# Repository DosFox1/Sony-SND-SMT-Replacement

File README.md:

# Sony-SND-SMT-Replacement
BETA -
A replacement for the Sony SND IC (part number 343-0045-A) as used on the Macintosh Plus, SE and others, using SMD parts.

# So what is it?
This is a variant of my existing Sony SND replacement, however, it uses purely SMD parts. 
My original repo for the through hole variant can be found here:
https://github.com/DosFox1/Sony-SND-THT-Replacement

The design is effectively the same - tincluding the annoying requirement to tap -12v from the board. If it aint broke, don't fix it!
Turns out removing -12v makes the audio output unhappy. So make sure you leave that in. 
POR works though - just make sure the pullup resistor from the POR switch is removed (I.E, R21 on the Mac Plus board). 

**NOTE - This is Completely Untested**
# Bill Of Materials:
```blocks
Part     Value          Device                       Package  Library                Sheet

C1       100n 16V       100N_CAP_0603                C0603    Capacitors SMD         1
C2       100n 16V       100N_CAP_0603                C0603    Capacitors SMD         1
C3       100n 16V       100N_CAP_0603                C0603    Capacitors SMD         1
C4       100n 16V       100N_CAP_0603                C0603    Capacitors SMD         1
C5       1u 16V         1U_CAP_0603                  C0603    Capacitors SMD         1
C6       100n 16V       100N_CAP_0603                C0603    Capacitors SMD         1
C7       470p           470P_CAP_0603                C0603    Capacitors SMD         1
C8       1n 50V         1N_CAP_0603                  C0603    Capacitors SMD         1
C9       100n 16V       100N_CAP_0603                C0603    Capacitors SMD         1
C10      100n 16V       100N_CAP_0603                C0603    Capacitors SMD         1
C11      220p           220P_CAP_0603                C0603    Capacitors SMD         1
C12      100n 16V       100N_CAP_0603                C0603    Capacitors SMD         1
D1       5.1V           DIODE-ZENER-MMSZ5231B        SOD-123  SparkFun-DiscreteSemi  1
IC1      TL072          OPAMP-DUALU                  SO08     SparkFun-IC-Amplifiers 1
IC2      4016D          4016D                        SO14     40xx                   1
IC3      NE555DRG4      555_SOIC8                    SOIC8    ICs                    1
IC4      74LVC1G06DBV   74LVC1G06DBV                 SOT23-5  74xx-little-us         1
IC5      Turned pins    SND THT turned pins          DIP16    Pins                   1
Q1       MMBT3906       TRANS_PNP-PMBT3906|MMBT3906L SOT23-3  SparkFun-DiscreteSemi  1
Q2       MMBT3904       TRANS_NPN-MMBT2222AL         SOT23-3  SparkFun-DiscreteSemi  1
R1       1M             GENERIC_RESISTOR_0603        R0603    Resistors SMD          1
R2       1M             GENERIC_RESISTOR_0603        R0603    Resistors SMD          1
R3       6K8            GENERIC_RESISTOR_0603        R0603    Resistors SMD          1
R4       47K            47K_RESISTOR                 R0603    Resistors SMD          1
R5       1k             1K_RESISTOR_0603             R0603    Resistors SMD          1
R6       47K            47K_RESISTOR                 R0603    Resistors SMD          1
R7       68K            GENERIC_RESISTOR_0603        R0603    Resistors SMD          1
R8       150K           GENERIC_RESISTOR_0603        R0603    Resistors SMD          1
R9       470K           GENERIC_RESISTOR_0603        R0603    Resistors SMD          1
R10      470K           GENERIC_RESISTOR_0603        R0603    Resistors SMD          1
R11      200K           GENERIC_RESISTOR_0603        R0603    Resistors SMD          1
R12      150R           150R_RESISTOR_0603           R0603    Resistors SMD          1
```

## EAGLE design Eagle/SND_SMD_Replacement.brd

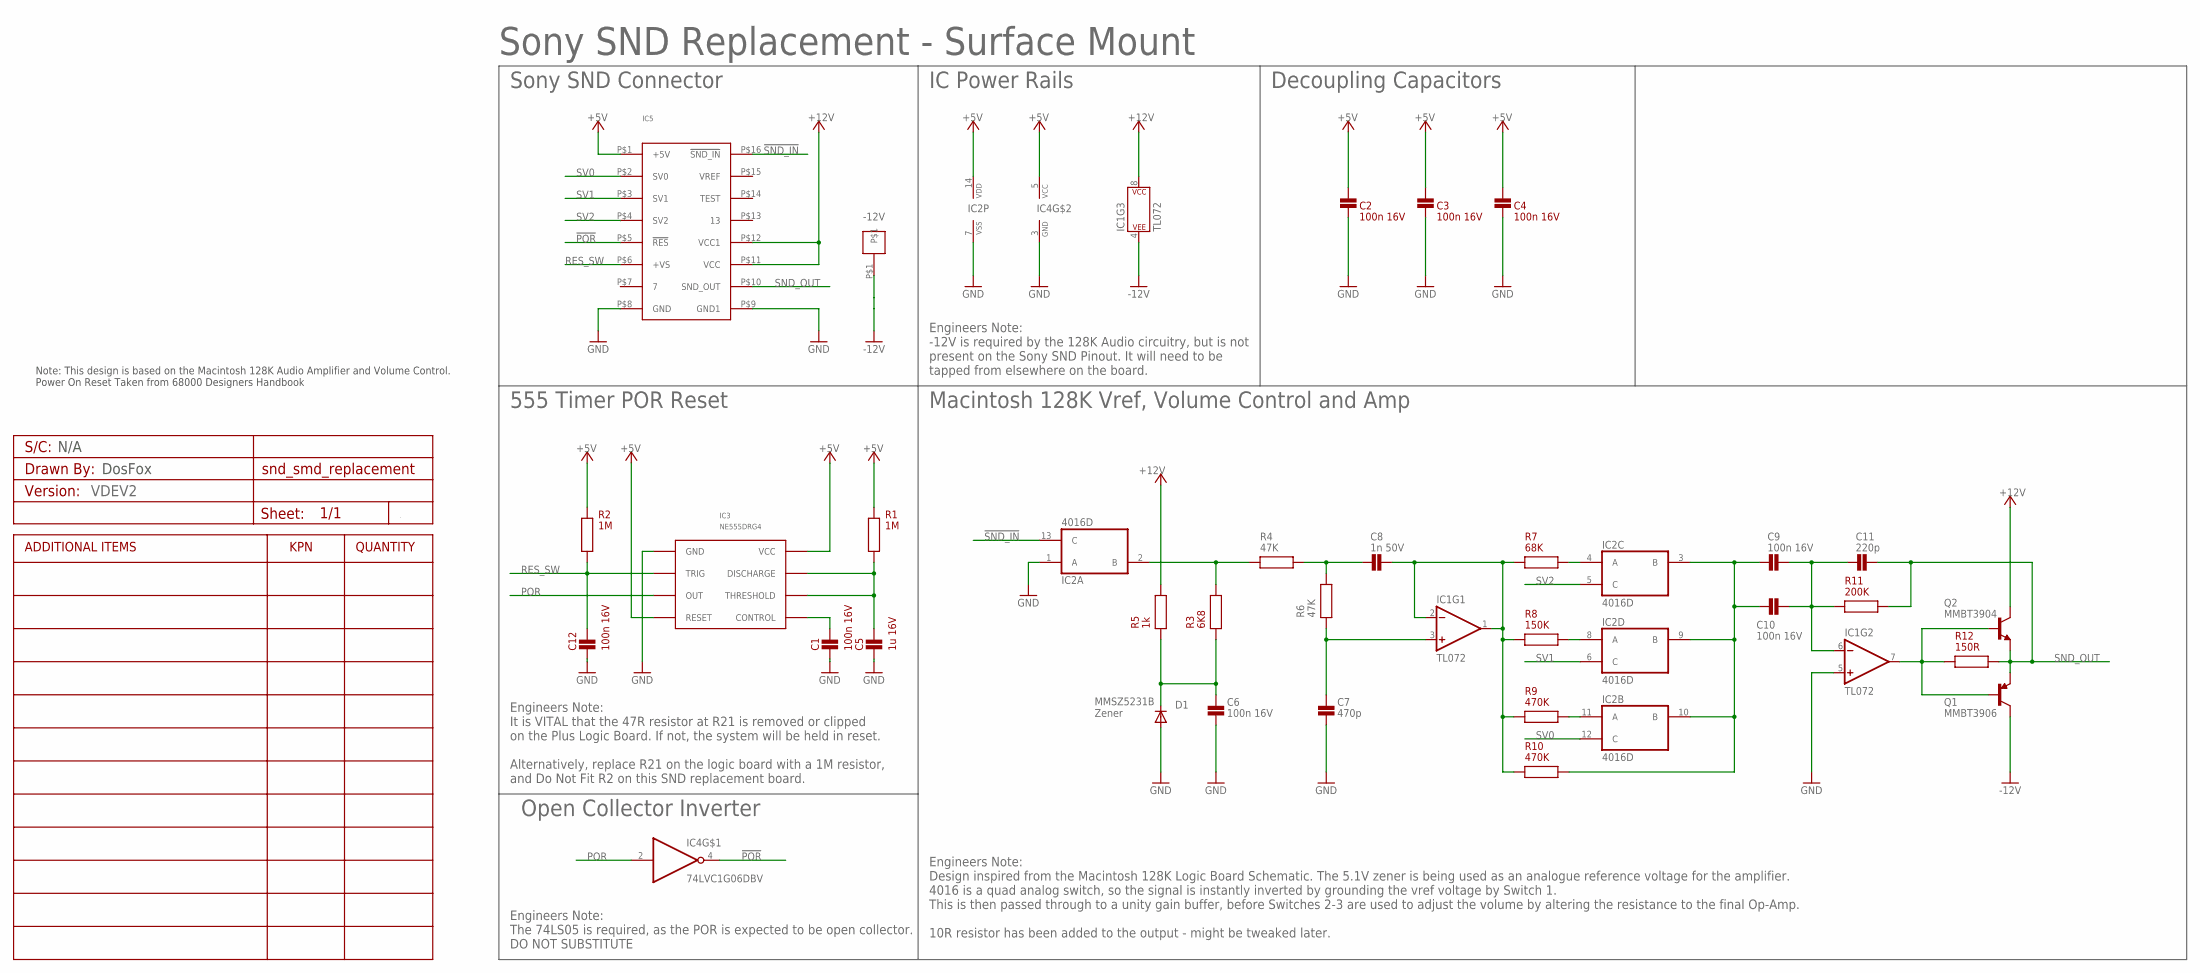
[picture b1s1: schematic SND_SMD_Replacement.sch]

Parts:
-12V: PADS_1W_SMD; SINGLE_CONN_SMD
A1: VDEV2; PCB_CUSTOM_DETAILS
C1, C2, C3, C4, C6, C9, C10, C12: 100n 16V; C0603
C5: 1u 16V; C0603
C7: 470p; C0603
C8: 1n 50V; C0603
C11: 220p; C0603
D1: 5.1V; SOD-123
IC1: TL072; SO08
IC2: 4016D; SO14
IC3: NE555DRG4; SOIC8
IC4: 74LVC1G06DBV; SOT23-5
IC5: SND; DIP16
Q1: MMBT3906; SOT23-3
Q2: MMBT3904; SOT23-3
R1, R2: 1M; R0603
R3: 6K8; R0603
R4, R6: 47K; R0603
R5: 1k; R0603
R7: 68K; R0603
R8: 150K; R0603
R9, R10: 470K; R0603
R11: 200K; R0603
R12: 150R; R0603

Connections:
!POR: IC4.4 (O), IC5.P$5 (!RES)
!SND_IN: IC2.13 (C), IC5.P$16 (!SND_IN)
+5V: C2.2, C3.2, C4.2, IC2.14 (VDD), IC3.P$4 (RESET), IC3.P$8 (VCC), IC4.5 (VCC), IC5.P$1 (+5V), R1.2, R2.2
+12V: IC1.8 (P$V+), IC5.P$11 (VCC), IC5.P$12 (VCC1), Q2.3 (C), R5.2
-12V: -12V.P$1, IC1.4 (P$V-), Q1.3 (C)
GND: C1.1, C2.1, C3.1, C4.1, C5.1, C6.1, C7.1, C12.1, D1.A, IC1.5 (+IN), IC2.1 (A), IC2.7 (VSS), IC3.P$1 (GND), IC4.3 (GND), IC5.P$8 (GND), IC5.P$9 (GND1)
unnamed: IC2.2 (B), R3.2, R4.1
unnamed: C9.1, C10.1, IC2.3 (B), IC2.9 (B), IC2.10 (B), R10.2
unnamed: C8.1, R4.2, R6.2
unnamed: C6.2, D1.C, R3.1, R5.1
unnamed: C7.2, IC1.3 (+IN), R6.1
unnamed: IC2.4 (A), R7.2
unnamed: IC2.8 (A), R8.2
unnamed: IC2.11 (A), R9.2
unnamed: C9.2, C10.2, C11.1, IC1.6 (-IN), R11.1
unnamed: C5.2, IC3.P$6 (THRESHOLD), IC3.P$7 (DISCHARGE), R1.1
unnamed: C8.2, IC1.1 (OUT), IC1.2 (-IN), R7.1, R8.1, R9.1, R10.1
unnamed: IC1.7 (OUT), Q1.1 (B), Q2.1 (B), R12.1
unnamed: C1.2, IC3.P$5 (CONTROL)
POR: IC3.P$3 (OUT), IC4.2 (I)
RES_SW: C12.2, IC3.P$2 (TRIG), IC5.P$6 (+VS), R2.1
SND_OUT: C11.2, IC5.P$10 (SND_OUT), Q1.2 (E), Q2.2 (E), R11.2, R12.2
SV0: IC2.12 (C), IC5.P$2 (SV0)
SV1: IC2.6 (C), IC5.P$3 (SV1)
SV2: IC2.5 (C), IC5.P$4 (SV2)

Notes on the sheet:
Note: This design is based on the Macintosh 128K Audio Amplifier and Volume Control. Power On Reset Taken from 68000 Designers Handbook
DosFox
N/A
MMSZ5231B Zener
Sony SND Replacement - Surface Mount
Sony SND Connector
IC Power Rails
Decoupling Capacitors
555 Timer POR Reset
Open Collector Inverter
Macintosh 128K Vref, Volume Control and Amp
Engineers Note: Design inspired from the Macintosh 128K Logic Board Schematic. The 5.1V zener is being used as an analogue reference voltage for the amplifier. 4016 is a quad analog switch, so the signal is instantly inverted by grounding the vref voltage by Switch 1. This is then passed through to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
Engineers Note: It is VITAL that the 47R resistor at R21 is removed or clipped on the Plus Logic Board. If not, the system will be held in reset. Alternatively, replace R21 on the logic board with a 1M resistor, and Do Not Fit R2 on this SND replacement board.
Engineers Note: The 74LS05 is required, as the POR is expected to be open collector. DO NOT SUBSTITUTE
Engineers Note: -12V is required by the 128K Audio circuitry, but is not present on the Sony SND Pinout. It will need to be tapped from elsewhere on the board.

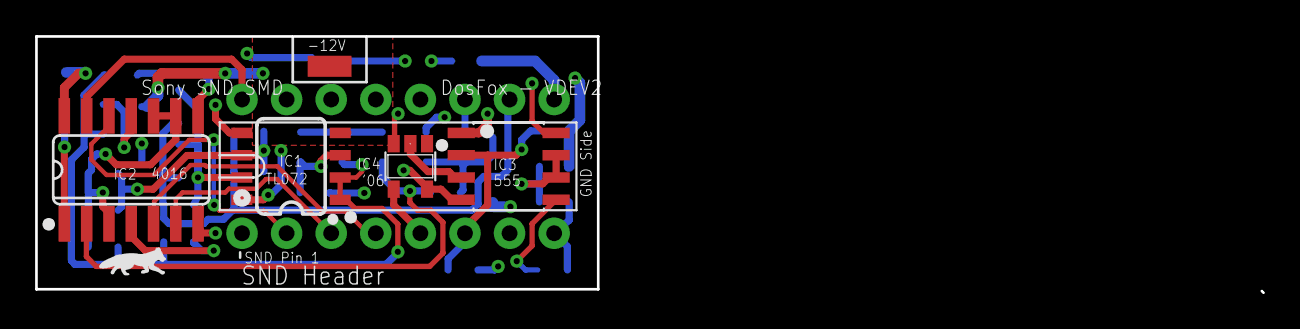
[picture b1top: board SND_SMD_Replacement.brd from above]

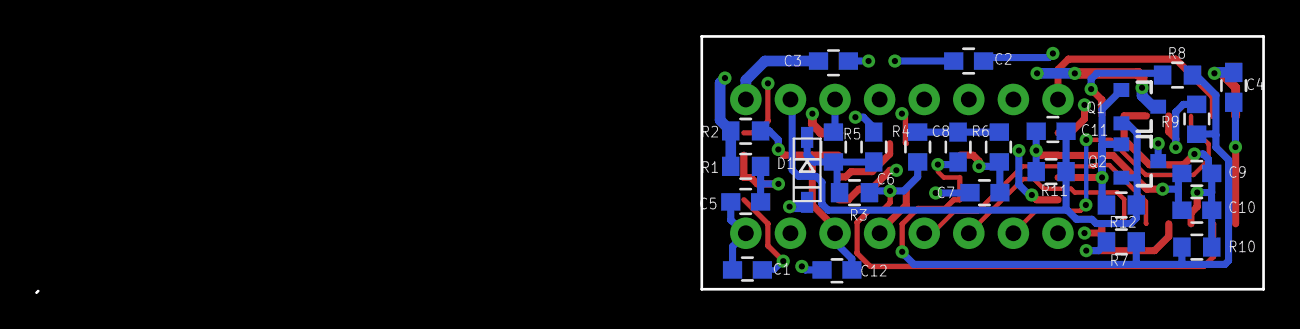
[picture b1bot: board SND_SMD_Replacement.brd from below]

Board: 4 copper layers, 69.9 x 14.6 mm, 34 parts (27 on the bottom side), 25 nets.

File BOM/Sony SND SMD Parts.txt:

Partlist

Exported from SND_SMD_Replacement.sch at 25/Oct/24 14:49

EAGLE Version 9.6.2 Copyright (c) 1988-2020 Autodesk, Inc.

Assembly variant: 

Part     Value          Device                       Package  Library                Sheet

C1       100n 16V       100N_CAP_0603                C0603    Capacitors SMD         1
C2       100n 16V       100N_CAP_0603                C0603    Capacitors SMD         1
C3       100n 16V       100N_CAP_0603                C0603    Capacitors SMD         1
C4       100n 16V       100N_CAP_0603                C0603    Capacitors SMD         1
C5       1u 16V         1U_CAP_0603                  C0603    Capacitors SMD         1
C6       100n 16V       100N_CAP_0603                C0603    Capacitors SMD         1
C7       470p           470P_CAP_0603                C0603    Capacitors SMD         1
C8       1n 50V         1N_CAP_0603                  C0603    Capacitors SMD         1
C9       100n 16V       100N_CAP_0603                C0603    Capacitors SMD         1
C10      100n 16V       100N_CAP_0603                C0603    Capacitors SMD         1
C11      220p           220P_CAP_0603                C0603    Capacitors SMD         1
C13      100n 16V       100N_CAP_0603                C0603    Capacitors SMD         1
D1       5.1V           DIODE-ZENER-MMSZ5231B        SOD-323  SparkFun-DiscreteSemi  1
IC1      LM358          OPAMP-DUALU                  SO08     SparkFun-IC-Amplifiers 1
IC2      4016D          4016D                        SO14     40xx                   1
IC3      NE555DRG4      555_SOIC8                    SOIC8    ICs                    1
IC4      74LVC1G06DBV   74LVC1G06DBV                 SOT23-5  74xx-little-us         1
IC5                     SND                          DIP16    ICs                    1
Q1       MMBT3906       TRANS_PNP-PMBT3906|MMBT3906L SOT23-3  SparkFun-DiscreteSemi  1
Q2       MMBT3904       TRANS_NPN-MMBT2222AL         SOT23-3  SparkFun-DiscreteSemi  1
R1       1M             GENERIC_RESISTOR_0603        R0603    Resistors SMD          1
R2       1M             GENERIC_RESISTOR_0603        R0603    Resistors SMD          1
R3       6K8            GENERIC_RESISTOR_0603        R0603    Resistors SMD          1
R4       47K            47K_RESISTOR                 R0603    Resistors SMD          1
R5       1k             1K_RESISTOR_0603             R0603    Resistors SMD          1
R6       47K            47K_RESISTOR                 R0603    Resistors SMD          1
R7       68K            GENERIC_RESISTOR_0603        R0603    Resistors SMD          1
R8       150K           GENERIC_RESISTOR_0603        R0603    Resistors SMD          1
R9       470K           GENERIC_RESISTOR_0603        R0603    Resistors SMD          1
R10      470K           GENERIC_RESISTOR_0603        R0603    Resistors SMD          1
R11      200K           GENERIC_RESISTOR_0603        R0603    Resistors SMD          1
R12      150R           150R_RESISTOR_0603           R0603    Resistors SMD          1

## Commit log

2024-11-25 Add files via upload
    Added License
2024-11-25 Update README.md
    initial readme update
2024-11-25 Add files via upload
    Initial commit of files and associated directories - VDEV1 not tested still.
2024-11-25 Update README.md
    updated readme
2024-11-29 Add files via upload
    oops. Fixed output of gerbers being four layers instead of two.
2024-12-02 Add files via upload
    Exported gerbers via KiCAD, EAGLE doesn't like four layer boards.
    Fingers crossed this works (sorry!)
2025-08-29 Updated README with VDEV2
    VDEV2 BOM and new photos added
2025-08-29 Added VDEV2 design (hopefully working)
2025-12-17 Update README.md
    Corrected typo for C12

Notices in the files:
parts and their libraries:
SparkFun-DiscreteSemi: Licensing: Creative Commons ShareAlike 4.0 International - https://creativecommons.org/licenses/by-sa/4.0
